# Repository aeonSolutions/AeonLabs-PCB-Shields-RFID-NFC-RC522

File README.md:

# AeonLabs PCB Shields RFID NFC RC522
This is a pcb design shield for RFID NFC RC522 reader writer. Suitable as a add-on design for any other KiCad project.

*Don't forget to LIKE , SHARE and subscribe the free whatsApp group* and if you liked this PCB consider buying me a cup of coffee. Links below.

### Status
  Waiting for first batch from factory. Not tested.

If you already tested this PCB send me a message. Thank you

## Revisions
- revision 1.0
 
## Download options
Download this repository if you need the KiCad Files or, download the Gerber files in the release section of this repository

## Liked it ? Get a Free PCB for yourself
Send me your Device or hardware and i will design a custom PCB for it. Free of charge. Contact-me on WhatsApp or email for more info. 

## Q&A WhatsApp Group
If you have any Questions or simply  like this kind of projects and want to stay updated with the latest research ideas and prototypes during the day and week, join the WhatsApp Group
[A.I. Things](https://chat.whatsapp.com/FkNC7u83kuy2QRA5sqjBVg)

## Fully assembled PCB
Alternatively, and if you do not want to build a PCB by yourself and like to buy one, you can do it here:

The price will be around 30eur plus postage fees.
(I will also deliver the assembled PCB with all the components in place at a fair aditonal cost).

This PCB is a #direct fit #replacement of the one found on the internet at sale. For example here: https://s.click.aliexpress.com/e/_9wRPxz

#### Be supportive of my dedication and work towards technology education and buy me a coffee. Link below.

________________________________________________________________________________________________________________

## PCB Parts list
- [Capacitor 2.2uF ](https://s.click.aliexpress.com/e/_AVdmzr)
- [Resistor SMD ](https://s.click.aliexpress.com/e/_A7OXrR)
- [NXP MFRC 522 IC](https://s.click.aliexpress.com/e/_Dc7RQn5)
- [27.12Mhz Crystal](https://s.click.aliexpress.com/e/_DFmHH83)

## Firmware Download 
one can use the PCB in the repository [AeonLabs-MCU-Burner-USB-to-UART-TTL](https://github.com/aeonSolutions/AeonLabs-MCU-Burner-USB-to-UART-TTL) to program the ESP32 WROOM32 MCU on this PCB.

______________________________________________________________________________________________________________________________

### License
2022 Creative Commons Attribution-NonCommercial-ShareAlike 4.0 International

https://creativecommons.org/licenses/by-nc-sa/4.0/

### Own a copy of this work
if you like to own a copy of this work, you can buy it as a NFT or Ethereum. contact me for more details at mtpsilva@gmail.com
________________________________________________________________________________________________________________
## [Go back to main catalogue page](https://github.com/aeonSolutions/PCB-Prototyping-Catalogue)
________________________________________________________________________________________________________________

### Share this PCB board files

### Be supportive of my dedication and work towards technology education and buy me a coffee

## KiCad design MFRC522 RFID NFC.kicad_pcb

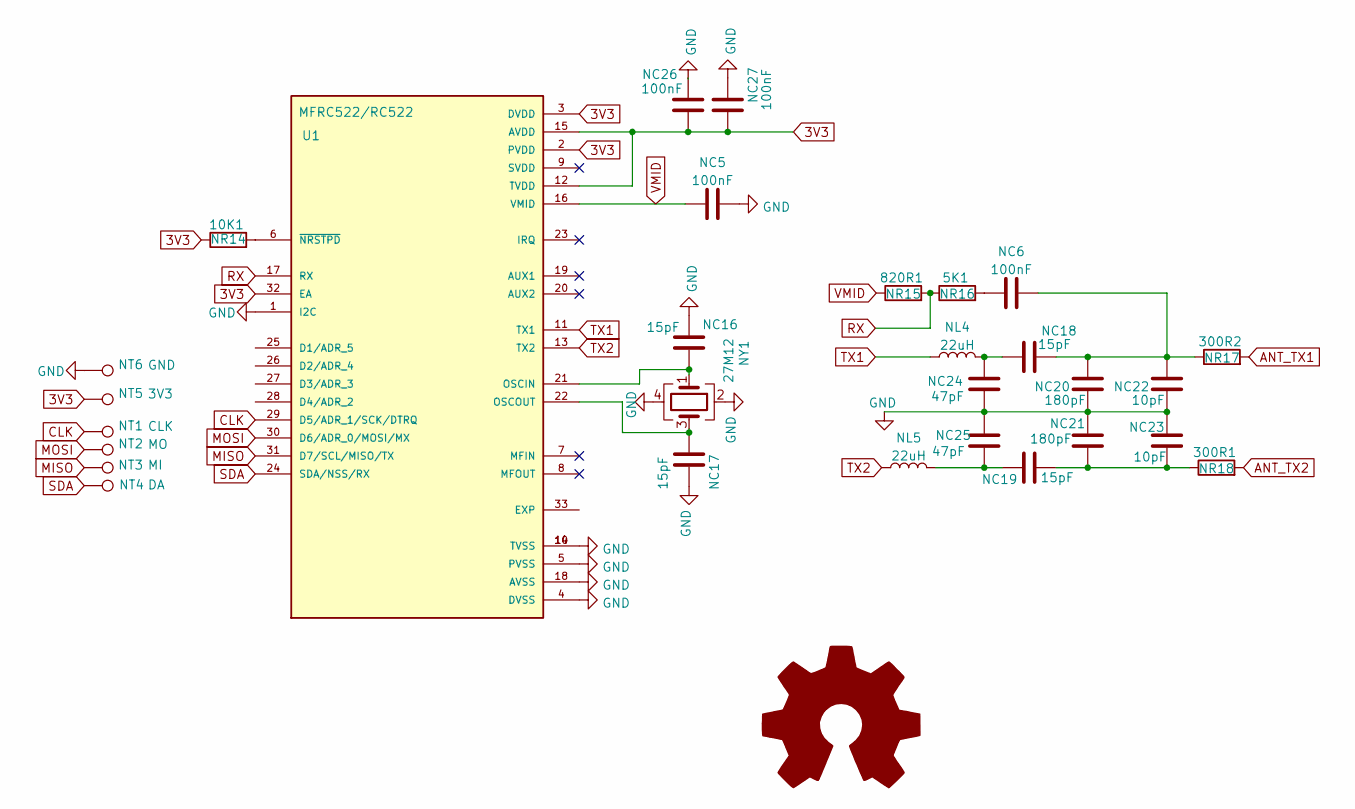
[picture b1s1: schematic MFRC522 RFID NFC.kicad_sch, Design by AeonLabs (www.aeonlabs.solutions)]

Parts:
5K1: NR16; R_0805_2012Metric_Pad1.20x1.40mm_HandSolder
10K1: NR14; R_0805_2012Metric_Pad1.20x1.40mm_HandSolder
300R1: NR18; R_0805_2012Metric_Pad1.20x1.40mm_HandSolder
300R2: NR17; R_0805_2012Metric_Pad1.20x1.40mm_HandSolder
820R1: NR15; R_0805_2012Metric_Pad1.20x1.40mm_HandSolder
NC5, NC6, NC26, NC27: 100nF; C_0805_2012Metric_Pad1.18x1.45mm_HandSolder
NC16, NC17, NC18, NC19: 15pF; C_0805_2012Metric_Pad1.18x1.45mm_HandSolder
NC20, NC21: 180pF; C_0805_2012Metric_Pad1.18x1.45mm_HandSolder
NC22, NC23: 10pF; C_0805_2012Metric_Pad1.18x1.45mm_HandSolder
NC24, NC25: 47pF; C_0805_2012Metric_Pad1.18x1.45mm_HandSolder
NL4, NL5: 22uH; L_0805_2012Metric_Pad1.15x1.40mm_HandSolder
NT1: CLK; TestPoint_Pad_1.0x1.0mm
NT2: MO; TestPoint_Pad_1.0x1.0mm
NT3: MI; TestPoint_Pad_1.0x1.0mm
NT4: DA; TestPoint_Pad_1.0x1.0mm
NT5: 3V3; TestPoint_Pad_1.0x1.0mm
NT6: GND; TestPoint_Pad_1.0x1.0mm
NY1: 27M12; Crystal_SMD_3225-4Pin_3.2x2.5mm_HandSoldering
U1: MFRC522/RC522; RC522 RFID NFC QFN50P500X500X100-33N; PARTREV 3.9

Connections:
3V3: 10K1.1, NC26.1, NC27.1, NT5.1, U1.2 (PVDD), U1.3 (DVDD), U1.12 (TVDD), U1.15 (AVDD), U1.32 (EA)
ANT_TX1: 300R2.2
ANT_TX2: 300R1.2
CLK: NT1.1, U1.29 (D5/ADR_1/SCK/DTRQ)
GND: NC5.2, NC16.2, NC17.2, NC20.2, NC21.1, NC22.2, NC23.1, NC24.2, NC25.1, NC26.2, NC27.2, NT6.1, NY1.2, NY1.4, U1.1 (I2C), U1.4 (DVSS), U1.5 (PVSS), U1.10 (TVSS), U1.14 (TVSS), U1.18 (AVSS)
MISO: NT3.1, U1.31 (D7/SCL/MISO/TX)
MOSI: NT2.1, U1.30 (D6/ADR_0/MOSI/MX)
unnamed: 5K1.2, NC6.1
unnamed: 10K1.2, U1.6 (~NRSTPD)
unnamed: NC16.1, NY1.1, U1.21 (OSCIN)
unnamed: NC17.1, NY1.3, U1.22 (OSCOUT)
unnamed: NC18.1, NC24.1, NL4.2
unnamed: 300R2.1, NC6.2, NC18.2, NC20.1, NC22.1
unnamed: NC19.1, NC25.2, NL5.2
unnamed: 300R1.1, NC19.2, NC21.2, NC23.2
RX: 5K1.1, 820R1.2, U1.17 (RX)
SDA: NT4.1, U1.24 (SDA/NSS/RX)
TX1: NL4.1, U1.11 (TX1)
TX2: NL5.1, U1.13 (TX2)
VMID: 820R1.1, NC5.1, U1.16 (VMID)

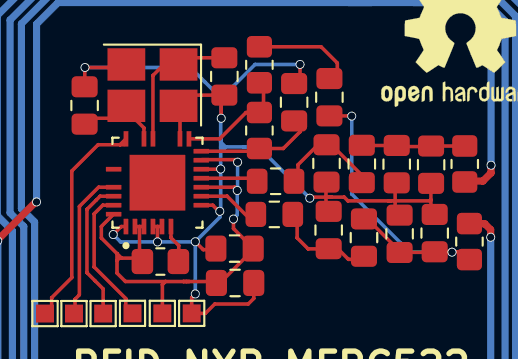
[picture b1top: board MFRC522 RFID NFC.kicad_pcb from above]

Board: 2 copper layers, 29 parts (0 on the bottom side), 18 nets.

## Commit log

2022-06-27 rev 1.0
2022-06-27 rev. 1.1
    added missing components
2022-06-27 revised
